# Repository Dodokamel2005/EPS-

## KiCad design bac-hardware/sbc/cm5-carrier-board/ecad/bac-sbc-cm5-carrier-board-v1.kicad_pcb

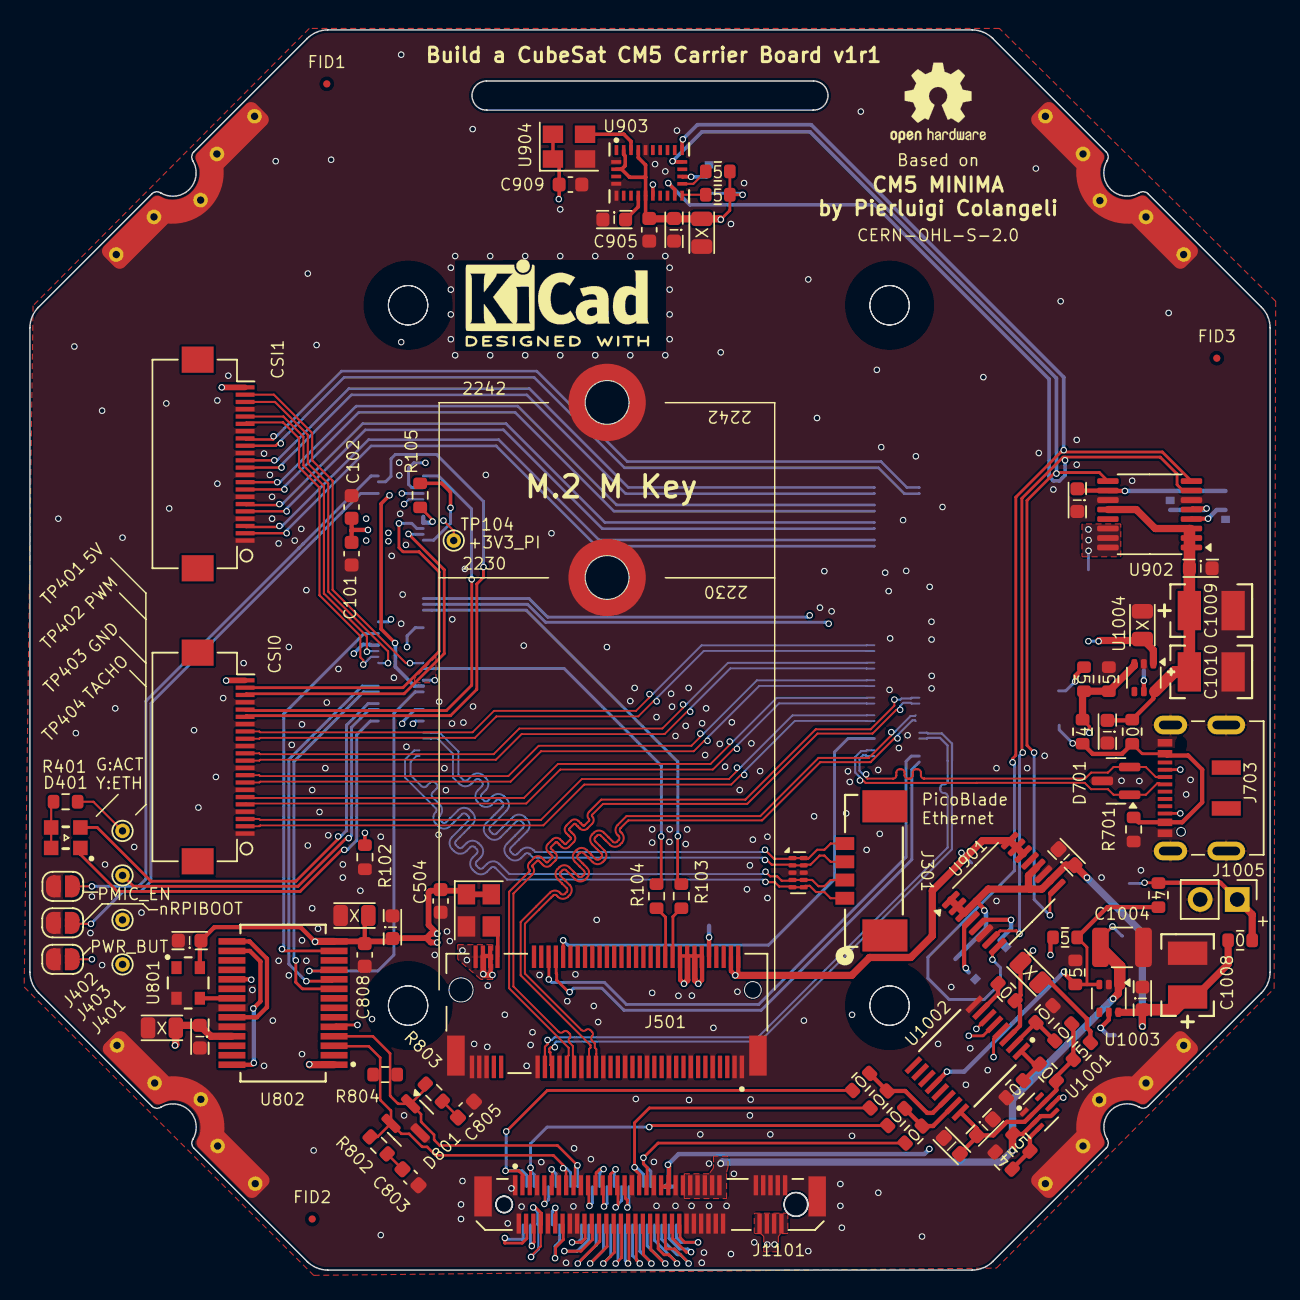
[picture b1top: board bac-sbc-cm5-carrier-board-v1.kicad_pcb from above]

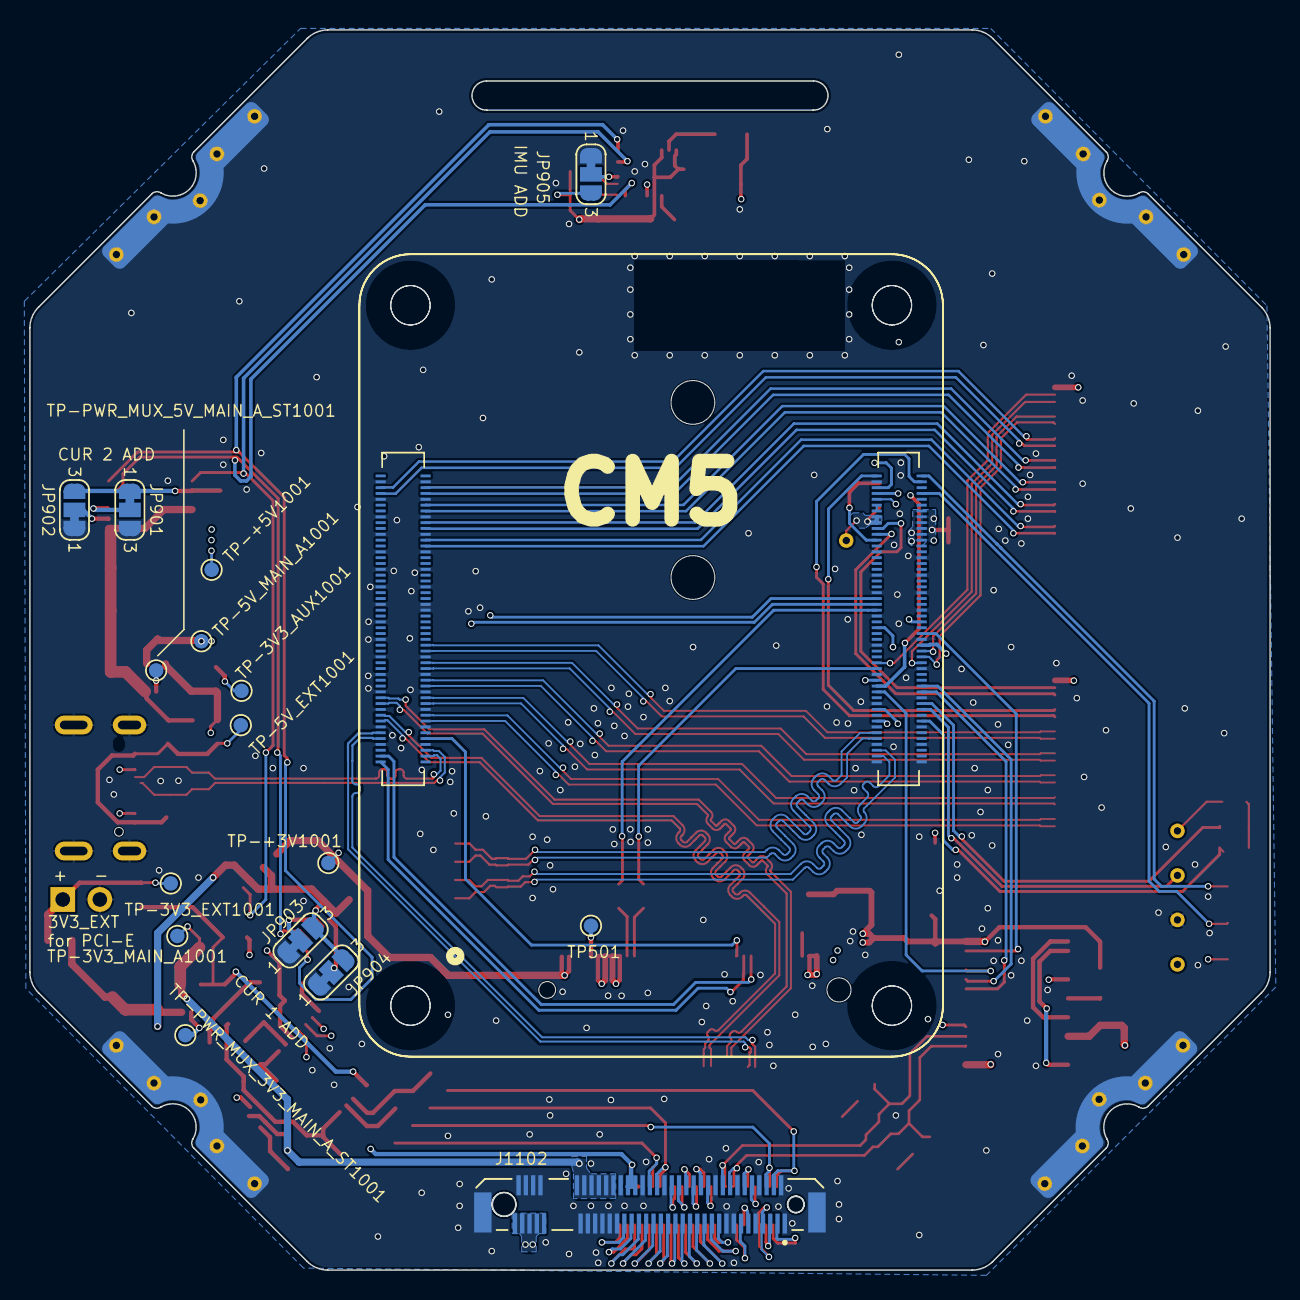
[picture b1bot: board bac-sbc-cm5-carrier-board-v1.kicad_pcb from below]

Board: 6 copper layers, 85.0 x 85.0 mm, 117 parts (18 on the bottom side), 143 nets.

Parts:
C101, C102, C504, C909: 100n; C_0603_1608Metric
C801, C804, C807, C901, C903, C904, C906, C908, C1003, C1006, C1007: 0.1u; bac-C-0603-0.1u
C802, C806, C907, C1002: 10u; bac-C-0805-10u
C803, C805, C808, C905: 560p; C_0603_1608Metric
C1001: 1u; bac-C-0603-1u
C1004: 22u; C_1210_3225Metric
C1005: 47u; bac-C-0805-10u
C1008, C1009, C1010: 47u; bac-C-1411
D401: WE 150080SG54050; WE-150080XX54050
D701: TI ESD752; SOT-23
D801: ESD752; SOT-23
FID1, FID2, FID3: Fiducial; Fiducial_0.5mm_Mask1mm
H1, H2, H3, H4: MountingHole_Pad; bac-PCB-Rail-Pad
J301: Molex 533984004; Molex-0533984004
J401, J402, J403: SolderJumper_2_Open; SolderJumper-2_P1.3mm_Open_RoundedPad1.0x1.5mm
J501: Bus_M.2_Socket_M; piecol-M.2-M-Key-socket-2230-2242
J601, J602: Conn_01x22_Female; piecol-Hirose-FH12-22S-0.5SH-1x22-1MP-P0.50mm-Horizontal
J703: TYPEC-305-ACP16H458; JAE-DX07S016JA1R1500
J1005: Conn_01x02_Socket; PinHeader_1x02_P2.54mm_Vertical
J1101, J1102: MDT350M01001VT; AMP-MDT350M01001VT
JP901, JP902, JP903, JP904, JP905: SolderJumper_3_Bridged12; SolderJumper-3_P1.3mm_Bridged12_RoundedPad1.0x1.5mm_NumberL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
M501: M2.5 Solder Nut 2230; WE-9774025243R
M502: M2.5 Solder Nut 2242; WE-9774025243R
Module201: ComputeModule5-CM5; piecol-Raspberry-Pi-5-Compute-Module-GPIO
Module202: ComputeModule5-CM5; piecol-Raspberry-Pi-5-Compute-Module-HSS
R102, R701: 10k; R_0603_1608Metric
R103, R104, R105: 0R; R_0603_1608Metric
R401: 2k2; R_0603_1608Metric
R802, R803, R804: 120; R_0603_1608Metric
R901, R902, R1001, R1013, R1015, R1016, R1017, R1018: 100k; bac-R-0603-100k
R1002, R1019, R1020: 10k; bac-R-0603-10k
R1003, R1004, R1005, R1006, R1007, R1008, R1010, R1011, R1014, R1021, R1022: 0; bac-R-0603-0
TP104: +3V3_PI; TestPoint_THTPad_D1.0mm_Drill0.5mm
TP401, TP402, TP403, TP404: GND; TestPoint_THTPad_D1.0mm_Drill0.5mm
TP501: GND; TestPoint_Pad_D1.0mm
TP-3V3_AUX1001: 3V3_AUX; TestPoint_Pad_D1.0mm
TP-3V3_EXT1001: 3V3_EXT; TestPoint_Pad_D1.0mm
TP-3V3_MAIN_A1001: 3V3_MAIN_A; TestPoint_Pad_D1.0mm
TP-5V_EXT1001: 5V_EXT; TestPoint_Pad_D1.0mm
TP-5V_MAIN_A1001: 5V_MAIN_A; TestPoint_Pad_D1.0mm
TP-+3V1001: +3V3; TestPoint_Pad_D1.0mm
TP-+5V1001: +5V; TestPoint_Pad_D1.0mm
TP-PWR_MUX_3V3_MAIN_A_ST1001: PWR_MUX_3V3_MAIN_A_ST; TestPoint_Pad_D1.0mm
TP-PWR_MUX_5V_MAIN_A_ST1001: PWR_MUX_5V_MAIN_A_ST; TestPoint_Pad_D1.0mm
U301: TPD4EUSB30; USON-10_2.5x1.0mm_P0.5mm
U503, U904: ASEK-32.768KHZ-L-R-T; Crystal_SMD_3225-4Pin_3.2x2.5mm
U801: SIT5000AI-2E-33N0-40.000000X; SIT-SIT5000AI-2E-33N0
U802: MCP251863T-H-SS; MT-MCP251863T-H-SS
U901, U902: INA260; TSSOP-16_4.4x5mm_P0.65mm
U903: BNO086; CEVA-BNO086
U1001: TPS2116DRL; TI-TPS2116DRL
U1002: TCAL9538PWR; TI-TCAL9538PWR
U1003, U1004: LM66100DCK; SOT-363_SC-70-6

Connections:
+1V8: Module201.88 (+1.8v_(Output)), Module201.90 (+1.8v_(Output))
+3V3: C504.1, C801.1, C806.1, C807.1, C808.1, J501.2 (3.3V), J501.4 (3.3V), J501.12 (3.3V), J501.14 (3.3V), J501.16 (3.3V), J501.18 (3.3V), J501.70 (3.3V), J501.72 (3.3V), J501.74 (3.3V), TP-+3V1001.1, U503.1 (EN), U503.4 (VDD), U801.4 (VDD), U802.1 (VIO), U802.14 (VDD), U901.14 (IN-), U901.15 (IN-), U901.16 (IN-)
+3V3_EXT: J1005.1, R1019.1, R1021.2, TP-3V3_EXT1001.1
+3V3_IN: C901.1, C903.1, C1006.1, C1008.1, JP901.1 (A), JP902.3 (B), JP903.3 (B), JP904.3 (B), R1021.1, U901.1 (IN+), U901.2 (IN+), U901.3 (IN+), U901.10 (VS), U901.12 (VBUS), U902.10 (VS), U1003.6 (VOUT)
+3V3_PI: C905.1, C906.1, C907.1, C909.1, J601.22, J602.22, JP905.3 (B), Module201.84 (+3.3v_(Output)), Module201.86 (+3.3v_(Output)), R105.1, R901.2, R902.2, TP104.1, U903.3 (VDD), U903.10 (CLKSEL0), U903.26 (XOUT32/CLKSEL1), U903.28 (VDDIO), U904.1 (EN), U904.4 (VDD)
+5V: C101.1, C102.1, C802.1, C804.1, Module201.77 (+5v_(Input)), Module201.79 (+5v_(Input)), Module201.81 (+5v_(Input)), Module201.83 (+5v_(Input)), Module201.85 (+5v_(Input)), Module201.87 (+5v_(Input)), R401.1, TP401.1, TP-+5V1001.1, U802.25 (VCC), U902.14 (IN-), U902.15 (IN-), U902.16 (IN-)
+5V_EXT: J703.A4 (VBUS), J703.A9 (VBUS), J703.B4 (VBUS), J703.B9 (VBUS), R701.1, R1020.1, R1022.2, TP-5V_EXT1001.1
+5V_IN: C904.1, C1007.1, C1009.1, C1010.1, R1022.1, U902.1 (IN+), U902.2 (IN+), U902.3 (IN+), U902.12 (VBUS), U1004.6 (VOUT)
/+3V3_AUX: J1101.41, J1101.43, J1102.42, J1102.44, R1015.1, R1017.1, TP-3V3_AUX1001.1, U1001.6 (VIN2)
/+3V3_MAIN_A: C1004.1, J1101.47, J1101.49, J1101.51, J1101.53, J1101.55, J1101.57, J1102.48, J1102.50, J1102.52, J1102.54, J1102.56, J1102.58, R1001.1, TP-3V3_MAIN_A1001.1, U1001.3 (VIN1), U1001.5 (MODE), U1003.1 (VIN)
/+5V_MAIN_A: C1005.1, J1101.68, J1101.70, J1101.72, J1101.74, J1102.67, J1102.69, J1102.71, J1102.73, J1102.75, TP-5V_MAIN_A1001.1, U1004.1 (VIN)
/BACBUS_A_CAN_1_N: D801.2 (K), J1101.15, J1102.16, R802.1, R804.2, U802.3 (CANL)
/BACBUS_A_CAN_1_P: D801.1 (K), J1101.17, J1102.18, R803.1, R804.1, U802.4 (CANH)
/BACBUS_A_I2C_1_SCL: J1101.3, J1102.4, R1008.1
/BACBUS_A_I2C_1_SDA: J1101.5, J1102.6, R1007.1
/BACBUS_A_I2C_2_SCL: J1101.35, J1102.36, R1011.2
/BACBUS_A_I2C_2_SDA: J1101.37, J1102.38, R1010.2
/CAN_1_CS: Module201.45 (GPIO24), U802.13 (~CS)
/CAN_1_INT: Module201.49 (GPIO18), U802.19 (~INT)
/CAN_1_PICO: Module201.27 (GPIO20), U802.10 (SDI)
/CAN_1_POCI: Module201.26 (GPIO19), U802.11 (SDO)
/CAN_1_SCL: Module201.25 (GPIO21), U802.9 (SCK)
/CAN_1_SHDN: Module201.48 (GPIO27), U802.5 (STBY)
/CM5/CAM0_GPIO0: J601.17, Module201.97 (CAM_GPIO0)
/CM5/CAM0_GPIO1: J601.18, Module201.100 (CAM_GPIO1)
/CM5/CC1: J703.A5 (CC1), Module201.94 (CC1)
/CM5/CC2: J703.B5 (CC2), Module201.96 (CC2)
/CM5/DPHY0_P.C_N: J601.8, Module202.127 (MIPI0_C_N)
/CM5/DPHY0_P.C_P: J601.9, Module202.129 (MIPI0_C_P)
/CM5/DPHY0_P.D0_N: J601.2, Module202.115 (MIPI0_D0_N)
/CM5/DPHY0_P.D0_P: J601.3, Module202.117 (MIPI0_D0_P)
/CM5/DPHY0_P.D1_N: J601.5, Module202.121 (MIPI0_D1_N)
/CM5/DPHY0_P.D1_P: J601.6, Module202.123 (MIPI0_D1_P)
/CM5/DPHY0_P.D2_N: J601.11, Module202.133 (MIPI0_D2_N)
/CM5/DPHY0_P.D2_P: J601.12, Module202.135 (MIPI0_D2_P)
/CM5/DPHY0_P.D3_N: J601.14, Module202.139 (MIPI0_D3_N)
/CM5/DPHY0_P.D3_P: J601.15, Module202.141 (MIPI0_D3_P)
/CM5/DPHY1_P.C_N: J602.8, Module202.187 (MIPI1_C_N)
/CM5/DPHY1_P.C_P: J602.9, Module202.189 (MIPI1_C_P)
/CM5/DPHY1_P.D0_N: J602.2, Module202.175 (MIPI1_D0_N)
/CM5/DPHY1_P.D0_P: J602.3, Module202.177 (MIPI1_D0_P)
/CM5/DPHY1_P.D1_N: J602.5, Module202.181 (MIPI1_D1_N)
/CM5/DPHY1_P.D1_P: J602.6, Module202.183 (MIPI1_D1_P)
/CM5/DPHY1_P.D2_N: J602.11, Module202.193 (MIPI1_D2_N)
/CM5/DPHY1_P.D2_P: J602.12, Module202.195 (MIPI1_D2_P)
/CM5/DPHY1_P.D3_N: J602.14, Module202.194 (MIPI1_D3_N)
/CM5/DPHY1_P.D3_P: J602.15, Module202.196 (MIPI1_D3_P)
/CM5/EEPROM_nWP: Module201.20 (EEPROM_nWP), R102.2
/CM5/ETH_PI.TRD0_N: J301.3, Module201.10 (Ethernet_Pair0_N), U301.2 (D1-), U301.9
/CM5/ETH_PI.TRD0_P: J301.4, Module201.12 (Ethernet_Pair0_P), U301.1 (D1+), U301.10
/CM5/ETH_PI.TRD1_N: J301.1, Module201.6 (Ethernet_Pair1_N), U301.5 (D2-), U301.6
/CM5/ETH_PI.TRD1_P: J301.2, Module201.4 (Ethernet_Pair1_P), U301.4 (D2+), U301.7
/CM5/ETH_nLED_ACTIVITY: D401.1, Module201.15 (Ethernet_nLED3(3.3v))
/CM5/GPIO4: Module201.54 (GPIO4), R103.2
/CM5/GPIO5: Module201.34 (GPIO5), R104.2
/CM5/GPIO7: J602.17, Module201.37 (GPIO7)
/CM5/GPIO8: J602.18, Module201.39 (GPIO8)
/CM5/GPIO_VREF: Module201.78 (GPIO_VREF(1.8v/3.3v_Input)), R105.2
/CM5/ID_SC: J602.20, Module201.35 (ID_SC)
/CM5/ID_SD: J602.21, Module201.36 (ID_SD)
/CM5/PCIE_PI.CLK_N: J501.53 (REFCLKn), Module202.112 (PCIe_CLK_N)
/CM5/PCIE_PI.CLK_P: J501.55 (REFCLKp), Module202.110 (PCIe_CLK_P)
/CM5/PCIE_PI.RX_N: J501.43 (PETp0), Module202.118 (PCIe_RX_N)
/CM5/PCIE_PI.RX_P: J501.41 (PETn0), Module202.116 (PCIe_RX_P)
/CM5/PCIE_PI.TX_N: J501.49 (PERp0), Module202.124 (PCIe_TX_N)
/CM5/PCIE_PI.TX_P: J501.47 (PERn0), Module202.122 (PCIe_TX_P)
/CM5/PCIE_PI.nCLKREQ: J501.52 (~CLKREQ), Module202.102 (PCIe_nCLKREQ)
/CM5/PCIE_PI.nRST: J501.50 (~PERST), Module202.109 (PCIe_nRST)
/CM5/PCIE_PI.nWAKE: J501.54 (~PEWAKE), Module202.104 (PCIE_nWAKE)
/CM5/PI_nLED_ACTIVITY: D401.2, Module201.21 (LED_nACT)
/CM5/PWM: Module201.19 (FAN_PWM), TP402.1
/CM5/SCL0: J601.20, Module201.80 (SCL0)
/CM5/SDA0: J601.21, Module201.82 (SDA0)
/CM5/TACHO: Module201.16 (FAN_TACHO), TP404.1
/CM5/USB_PI.D_N: D701.2 (K), J703.A7 (D-), Module202.103 (USB2_N)
/CM5/USB_PI.D_P: D701.1 (K), J703.B6 (D+), Module202.105 (USB2_P)
/CM5/nRPIBOOT: J402.2 (B), Module201.93 (nRPIBOOT)
/I2C_MUX_~RESET: C1002.2, Module201.41 (GPIO25), R1014.1, U1002.3 (~RESET)
/IMU_~RESET: Module201.28 (GPIO13), U903.11 (NRST)
/PCIe-M2/RX: J501.22 (NC), R104.1
/PCIe-M2/TX: J501.20 (NC), R103.1
/PMIC_EN: J403.1 (A), Module201.99 (PMIC_ENABLE), U1002.5 (P1)
/PWR_BUT: J401.1 (A), Module201.92 (PWR_BUT), U1002.6 (P2)
/Power Multiplexers/A_3V3_MAIN_~EN: R1015.2, R1016.1, R1019.2, U1002.12 (P7), U1003.3 (~CE)
/Power Multiplexers/A_5V_MAIN_~EN: R1017.2, R1018.1, R1020.2, U1002.4 (P8), U1004.3 (~CE)
/Power Multiplexers/A_ADD0: R1003.2, R1004.1, U1002.1 (A0)
/Power Multiplexers/A_ADD1: R1005.2, R1006.1, U1002.2 (A1)
/Power Multiplexers/A_P03: R1014.2, U1002.7 (P3)
/Power Multiplexers/A_SCL: R1008.2, R1011.1, U1002.14 (SCL)
/Power Multiplexers/A_SDA: R1007.2, R1010.1, U1002.15 (SDA)
/Power Multiplexers/A_VCC: C1001.1, C1003.1, R1003.1, R1005.1, R1013.1, U1001.2 (VOUT), U1001.7 (VOUT), U1002.16 (VCC)
/SCL: Module201.56 (GPIO3), U901.9 (SCL), U902.9 (SCL), U903.19 (H_SCL/SCK/RX)
/SDA: Module201.58 (GPIO2), U901.8 (SDA), U902.8 (SDA), U903.20 (H_SDA/H_POCI/TX)
/Sensors/CUR_1_ADD0: JP903.2 (C), U901.5 (A0)
/Sensors/CUR_1_ADD1: JP904.2 (C), U901.4 (A1)
/Sensors/CUR_2_ADD0: JP901.2 (C), U902.5 (A0)
/Sensors/CUR_2_ADD1: JP902.2 (C), U902.4 (A1)
/Sensors/ENV_SCL: R902.1, U903.15 (ENV_SCL)
/Sensors/ENV_SDA: R901.1, U903.16 (ENV_SDA)
/Sensors/IMU_32kHz: U903.27 (XIN32), U904.3 (Out)
/Sensors/IMU_ADD: JP905.2 (C), U903.17 (SA0/H_PICO)
/bacBus Connectors/3A: J1101.4, J1102.3
/bacBus Connectors/5A: J1101.6, J1102.5
/bacBus Connectors/7A: J1101.8, J1102.7
/bacBus Connectors/10A: J1101.9, J1102.10
/bacBus Connectors/11A: J1101.12, J1102.11
/bacBus Connectors/12A: J1101.11, J1102.12
/bacBus Connectors/13A: J1101.14, J1102.13
/bacBus Connectors/19A: J1101.20, J1102.19
/bacBus Connectors/21A: J1101.22, J1102.21
/bacBus Connectors/22A: J1101.21, J1102.22
/bacBus Connectors/23A: J1101.24, J1102.23
/bacBus Connectors/24A: J1101.23, J1102.24
/bacBus Connectors/25A: J1101.26, J1102.25
/bacBus Connectors/26A: J1101.25, J1102.26
/bacBus Connectors/27A: J1101.28, J1102.27
/bacBus Connectors/28A: J1101.27, J1102.28
/bacBus Connectors/29A: J1101.30, J1102.29
/bacBus Connectors/30A: J1101.29, J1102.30
/bacBus Connectors/31A: J1101.32, J1102.31
/bacBus Connectors/32A: J1101.31, J1102.32
/bacBus Connectors/33A: J1101.34, J1102.33
/bacBus Connectors/35A: J1101.36, J1102.35
/bacBus Connectors/37A: J1101.38, J1102.37
/bacBus Connectors/39A: J1101.40, J1102.39
/bacBus Connectors/41A: J1101.42, J1102.41
/bacBus Connectors/43A: J1101.44, J1102.43
/bacBus Connectors/45A: J1101.46, J1102.45
/~INT: Module201.30 (GPIO6), U901.7 (ALERT), U902.7 (ALERT), U903.14 (H_INTN)
GND: C101.2, C102.2, C504.2, C801.2, C802.2, C803.2, C804.2, C805.2, C806.2, C807.2, C808.2, C901.2, C903.2, C904.2, C905.2, C906.2, C907.2, C908.1, C909.2, C1001.2, C1003.2, C1004.2, C1005.2, C1006.2, C1007.2, C1008.2, C1009.2, C1010.2, D701.3 (A), D801.3 (A), H1.1, H2.1, H3.1, H4.1, J401.2 (B), J402.1 (A), J403.2 (B), J501.1 (GND), J501.3 (GND), J501.9 (GND), J501.15 (GND), J501.21 (GND), J501.27 (GND), J501.33 (GND), J501.39 (GND), J501.45 (GND), J501.51 (GND), J501.57 (GND), J501.71 (GND), J501.73 (GND), J501.75 (GND), J501.S1, J501.S2, J601.1, J601.4, J601.7, J601.10, J601.13, J601.16, J601.19, J602.1, J602.4, J602.7, J602.10, J602.13, J602.16, J602.19, J703.A1 (GND), J703.A12 (GND), J703.B1 (GND), J703.B12 (GND), J703.S1 (SHIELD), J1005.2, J1101.1, J1101.2, J1101.7, J1101.10, J1101.13, J1101.16, J1101.18, J1101.19, J1101.33, J1101.39, J1101.45, J1101.48, J1101.50, J1101.52, J1101.54, J1101.56, J1101.58, J1101.67, J1101.69, J1101.71, J1101.73, J1101.75, J1101.S1 (SHIELD), J1101.S2 (SHIELD__1), J1102.1, J1102.2, J1102.8, J1102.9, J1102.14, J1102.15, J1102.17, J1102.20, J1102.34, J1102.40, J1102.46, J1102.47, J1102.49, J1102.51, J1102.53, J1102.55, J1102.57, J1102.68, J1102.70, J1102.72, J1102.74, J1102.S1 (SHIELD), J1102.S2 (SHIELD__1), JP901.3 (B), JP902.1 (A), JP903.1 (A), JP904.1 (A), JP905.1 (A), M501.1, M502.1, Module201.1 (GND), Module201.2 (GND), Module201.7 (GND), Module201.8 (GND), Module201.13 (GND), Module201.14 (GND), Module201.22 (GND), Module201.23 (GND), Module201.32 (GND), Module201.33 (GND), Module201.42 (GND), Module201.43 (GND), Module201.52 (GND), Module201.53 (GND), Module201.59 (GND), Module201.60 (GND), Module201.65 (GND), Module201.66 (GND), Module201.71 (GND), Module201.74 (GND), Module201.98 (GND), Module202.107 (GND), Module202.108 (GND), Module202.113 (GND), Module202.114 (GND), Module202.119 (GND), Module202.120 (GND), Module202.125 (GND), Module202.126 (GND), Module202.131 (GND), Module202.132 (GND), Module202.137 (GND), Module202.138 (GND), Module202.144 (GND), Module202.150 (GND), Module202.153 (HDMI0_HOTPLUG), Module202.155 (GND), Module202.156 (GND), Module202.161 (GND), Module202.162 (GND), Module202.167 (GND), Module202.168 (GND), Module202.173 (GND), Module202.174 (GND), Module202.179 (GND), Module202.180 (GND), Module202.185 (GND), Module202.186 (GND), Module202.191 (GND), Module202.192 (GND), Module202.197 (GND), Module202.198 (GND), R102.1, R701.2, R1002.2, R1004.2, R1006.2, R1016.2, R1018.2, TP403.1, U301.3 (GND), U301.8 (GND), U503.2 (GND), U801.2 (GND), U802.22 (VSS), U802.24 (GND), U901.6 (GND), U901.11 (GND), U902.6 (GND), U902.11 (GND), U903.2 (GND), U903.5 (PS1), U903.6 (PS0/WAKE), U903.25 (GND), U904.2 (GND), U1001.1 (GND), U1002.8 (GND), U1003.2 (GND), U1004.2 (GND)
unnamed: C803.1, R802.2
unnamed: C805.1, R803.2
unnamed: C1002.1, R1013.2
unnamed: D401.3, D401.4, R401.2
unnamed: J501.10 (DAS/~DSS/~LED1), TP501.1
unnamed: J501.68 (SUSCLK), U503.3 (Out)
unnamed: U801.3 (OUT), U802.21 (OSC1)
unnamed: U802.16 (RXCAN), U802.28 (RXD)
unnamed: U802.15 (TXCAN), U802.23 (TXD)
unnamed: C908.2, U903.9 (CAP)
unnamed: R1001.2, R1002.1, U1001.4 (PR1)
unnamed: TP-PWR_MUX_3V3_MAIN_A_ST1001.1, U1003.5 (ST)
unnamed: TP-PWR_MUX_5V_MAIN_A_ST1001.1, U1004.5 (ST)

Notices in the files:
bac-hardware/sbc/cm5-carrier-board/ecad/bac-sbc-cm5-carrier-board-v1.kicad_pcb:
CERN-OHL-S-2.0
